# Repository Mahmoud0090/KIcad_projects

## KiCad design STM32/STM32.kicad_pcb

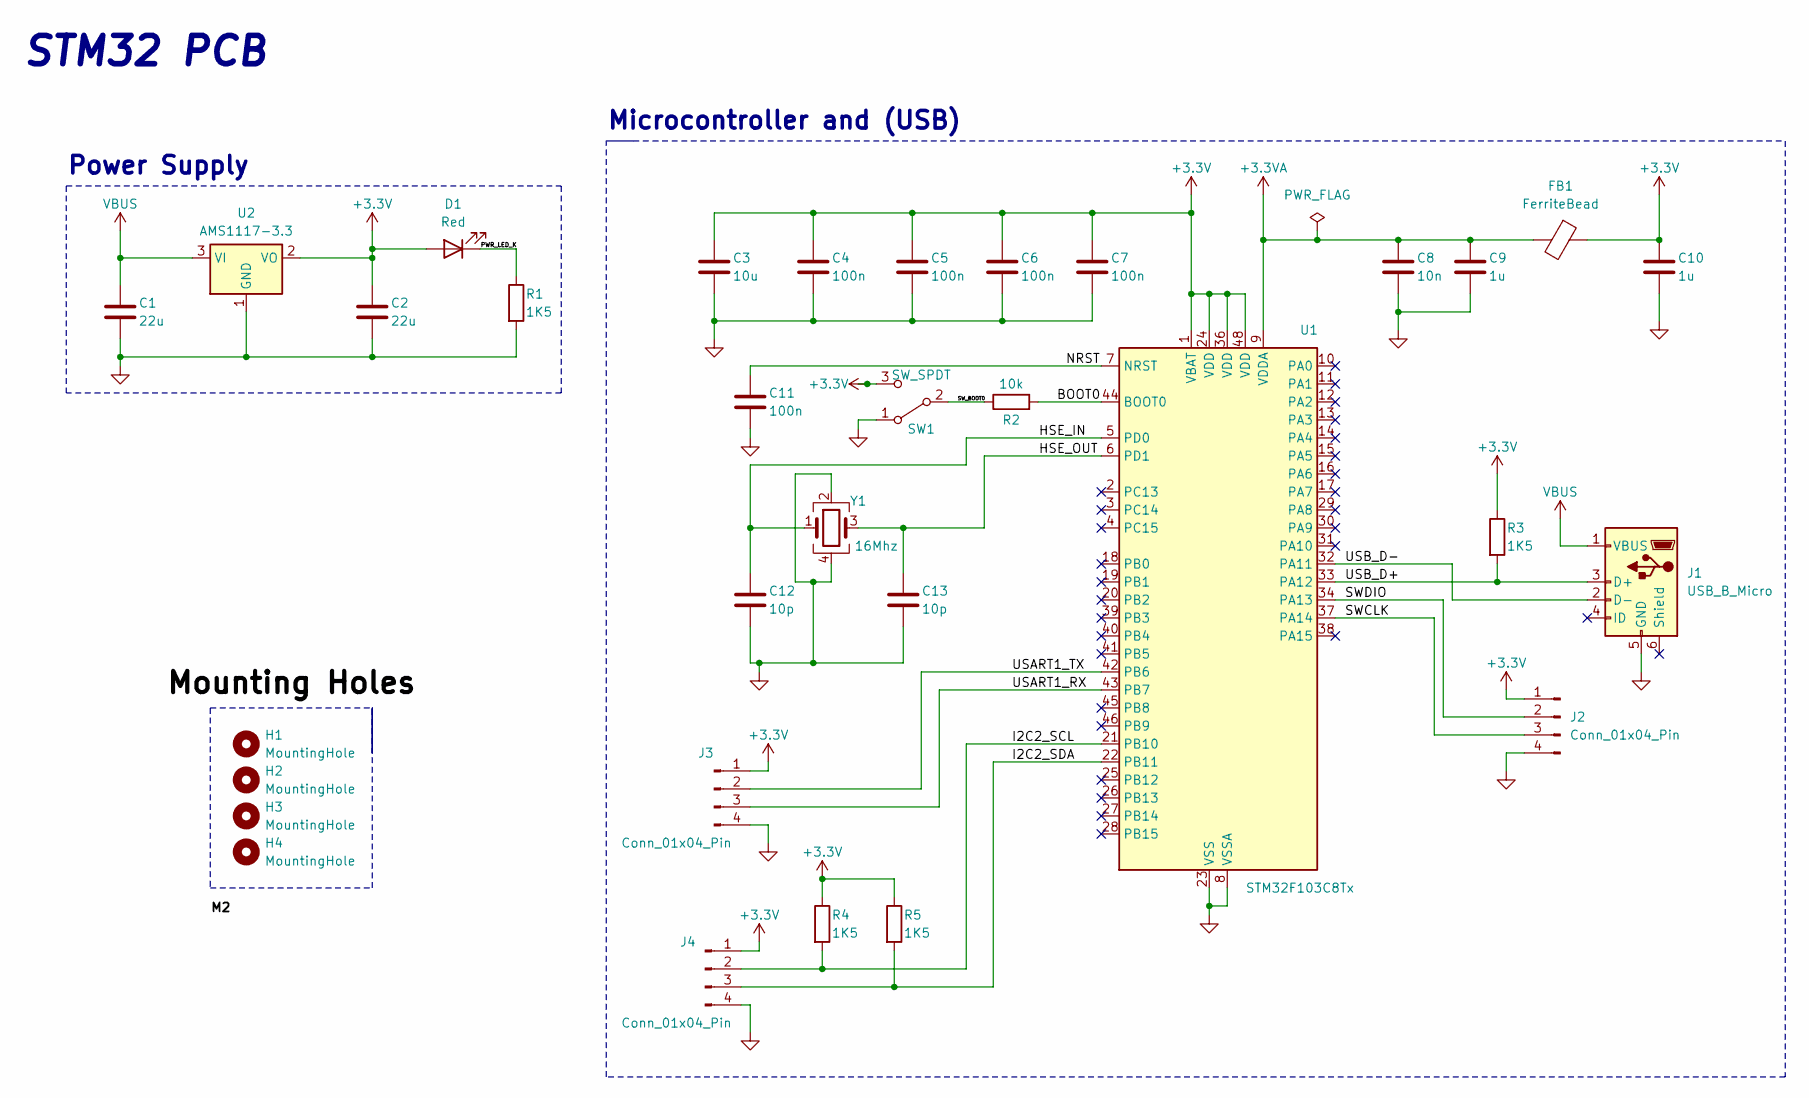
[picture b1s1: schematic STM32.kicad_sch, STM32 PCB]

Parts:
C1, C2: 22u; C_0805_2012Metric
C3: 10u; C_0603_1608Metric
C4, C5, C6, C7, C11: 100n; C_0402_1005Metric
C8: 10n; C_0402_1005Metric
C9, C10: 1u; C_0402_1005Metric
C12, C13: 10p; C_0402_1005Metric
D1: Red; LED_0603_1608Metric
FB1: FerriteBead; L_0603_1608Metric
H1, H2, H3, H4: MountingHole; MountingHole_2.2mm_M2
J1: USB_B_Micro; USB_Micro-B_Wuerth_629105150521
J2, J3, J4: Conn_01x04_Pin; PinHeader_1x04_P2.54mm_Vertical
R1, R3, R4, R5: 1K5; R_0402_1005Metric
R2: 10k; R_0402_1005Metric
SW1: SW_SPDT; SW_SPDT_PCM12
U1: STM32F103C8Tx; LQFP-48_7x7mm_P0.5mm
U2: AMS1117-3.3; SOT-223-3_TabPin2
Y1: 16Mhz; Crystal_SMD_3225-4Pin_3.2x2.5mm

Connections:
+3.3V: C2.1, C3.1, C4.1, C5.1, C6.1, C7.1, C10.1, D1.2 (A), FB1.1, J2.1, J3.1, J4.1, R3.1, R4.1, R5.1, SW1.3 (C), U1.1 (VBAT), U1.24 (VDD), U1.36 (VDD), U1.48 (VDD), U2.2 (VO)
+3.3VA: C8.1, C9.1, FB1.2, U1.9 (VDDA)
/BOOT0: R2.2, U1.44 (BOOT0)
/HSE_IN: C12.1, U1.5 (PD0), Y1.1
/HSE_OUT: C13.1, U1.6 (PD1), Y1.3
/I2C2_SCL: J4.2, R4.2, U1.21 (PB10)
/I2C2_SDA: J4.3, R5.2, U1.22 (PB11)
/NRST: C11.1, U1.7 (NRST)
/PWR_LED_K: D1.1 (K), R1.1
/SWCLK: J2.3, U1.37 (PA14)
/SWDIO: J2.2, U1.34 (PA13)
/SW_BOOT0: R2.1, SW1.2 (B)
/USART1_RX: J3.3, U1.43 (PB7)
/USART1_TX: J3.2, U1.42 (PB6)
/USB_D+: J1.3 (D+), R3.2, U1.33 (PA12)
/USB_D-: J1.2 (D-), U1.32 (PA11)
GND: C1.2, C2.2, C3.2, C4.2, C5.2, C6.2, C7.2, C8.2, C9.2, C10.2, C11.2, C12.2, C13.2, J1.5 (GND), J2.4, J3.4, J4.4, R1.2, SW1.1 (A), U1.8 (VSSA), U1.23 (VSS), U1.35 (VSS), U1.47 (VSS), U2.1 (GND), Y1.2, Y1.4
VBUS: C1.1, J1.1 (VBUS), U2.3 (VI)

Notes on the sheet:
Microcontroller and (USB)
Power Supply
STM32 PCB

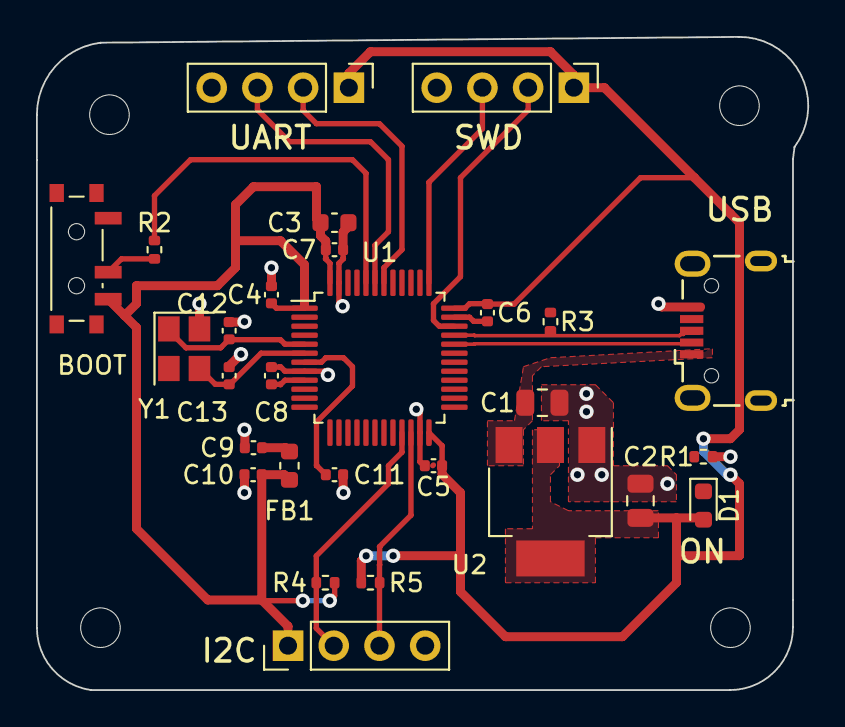
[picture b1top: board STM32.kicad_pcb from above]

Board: 2 copper layers, 42.9 x 36.3 mm, 32 parts (0 on the bottom side), 18 nets.

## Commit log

2023-08-23 STM32 tutorial-first project
